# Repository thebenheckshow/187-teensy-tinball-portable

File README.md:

# 187-teensy-tinball-portable

In this episode series Ben creates a mini pinball machine portable for this years Freescale Technology Forum in Austin,Texas. The pinball machine be half scale, will run off of the Teensy 3.1 and will have electronic music and scoring.

Visit the Ben Heck Community and Suggest a Build: http://www.element14.com/tbhs

Part 1: http://www.element14.com/community/docs/DOC-76788/l/episode-187-ben-heck-s-teensy-pinball-portable-part-1-episode

Part 2: http://www.element14.com/community/docs/DOC-77092/l/episode-189-ben-hecks-teensy-pinball-portable-part-2-episode

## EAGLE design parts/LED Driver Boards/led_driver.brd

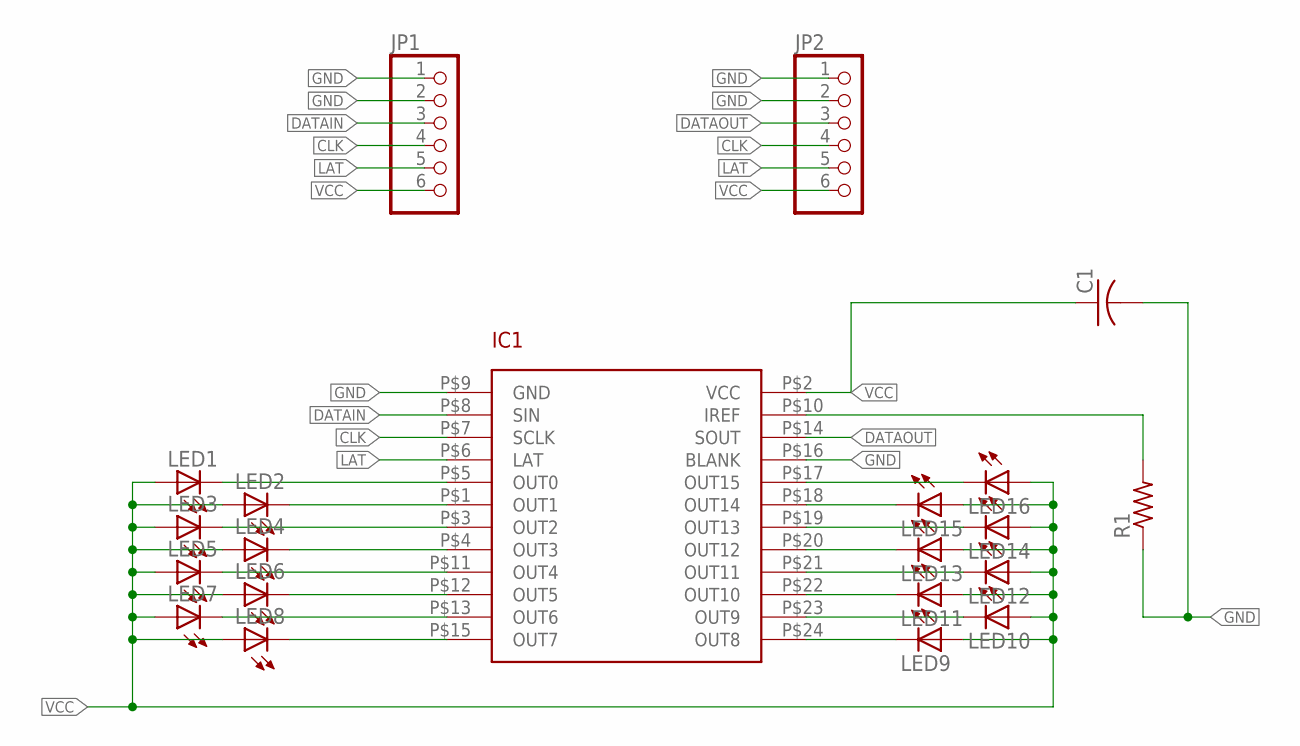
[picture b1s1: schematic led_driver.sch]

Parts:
C1: C-USC1206; C1206
IC1: TLC59282; SSOP-24
JP1, JP2: PINHD-1X6; 1X06
LED1, LED2, LED3, LED4, LED5, LED6, LED7, LED8, LED9, LED10, LED11, LED12, LED13, LED14, LED15, LED16: LED3MM
R1: R-US_0207/10; 0207/10

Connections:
CLK: IC1.P$7 (SCLK), JP1.4, JP2.4
DATAIN: IC1.P$8 (SIN), JP1.3
DATAOUT: IC1.P$14 (SOUT), JP2.3
GND: C1.2, IC1.P$9 (GND), IC1.P$16 (BLANK), JP1.1, JP1.2, JP2.1, JP2.2, R1.1
LAT: IC1.P$6 (LAT), JP1.5, JP2.5
unnamed: IC1.P$5 (OUT0), LED1.K (C)
unnamed: IC1.P$1 (OUT1), LED2.K (C)
unnamed: IC1.P$3 (OUT2), LED3.K (C)
unnamed: IC1.P$4 (OUT3), LED4.K (C)
unnamed: IC1.P$11 (OUT4), LED5.K (C)
unnamed: IC1.P$12 (OUT5), LED6.K (C)
unnamed: IC1.P$13 (OUT6), LED7.K (C)
unnamed: IC1.P$15 (OUT7), LED8.K (C)
unnamed: IC1.P$17 (OUT15), LED16.K (C)
unnamed: IC1.P$18 (OUT14), LED15.K (C)
unnamed: IC1.P$19 (OUT13), LED14.K (C)
unnamed: IC1.P$20 (OUT12), LED13.K (C)
unnamed: IC1.P$21 (OUT11), LED12.K (C)
unnamed: IC1.P$22 (OUT10), LED11.K (C)
unnamed: IC1.P$23 (OUT9), LED10.K (C)
unnamed: IC1.P$24 (OUT8), LED9.K (C)
unnamed: IC1.P$10 (IREF), R1.2
VCC: C1.1, IC1.P$2 (VCC), JP1.6, JP2.6, LED1.A, LED2.A, LED3.A, LED4.A, LED5.A, LED6.A, LED7.A, LED8.A, LED9.A, LED10.A, LED11.A, LED12.A, LED13.A, LED14.A, LED15.A, LED16.A

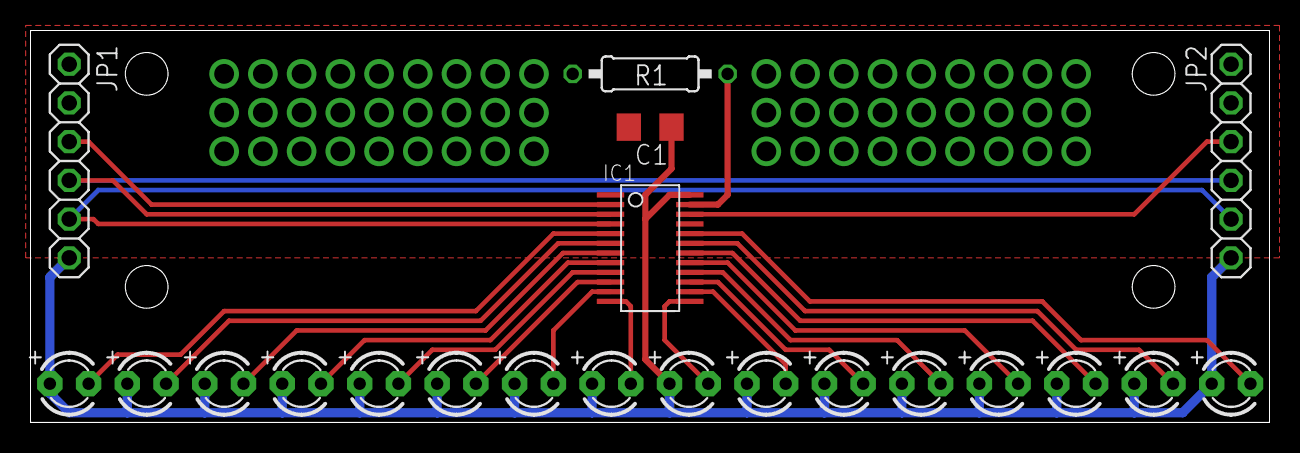
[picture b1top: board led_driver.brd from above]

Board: 4 copper layers, 81.3 x 25.7 mm, 21 parts (0 on the bottom side), 23 nets.

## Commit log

2015-11-05 Update README.md
    Removed incorrect tracking codes on links
2015-11-19 Fixed link in readme
    Previous link had incorrect tracking code.
